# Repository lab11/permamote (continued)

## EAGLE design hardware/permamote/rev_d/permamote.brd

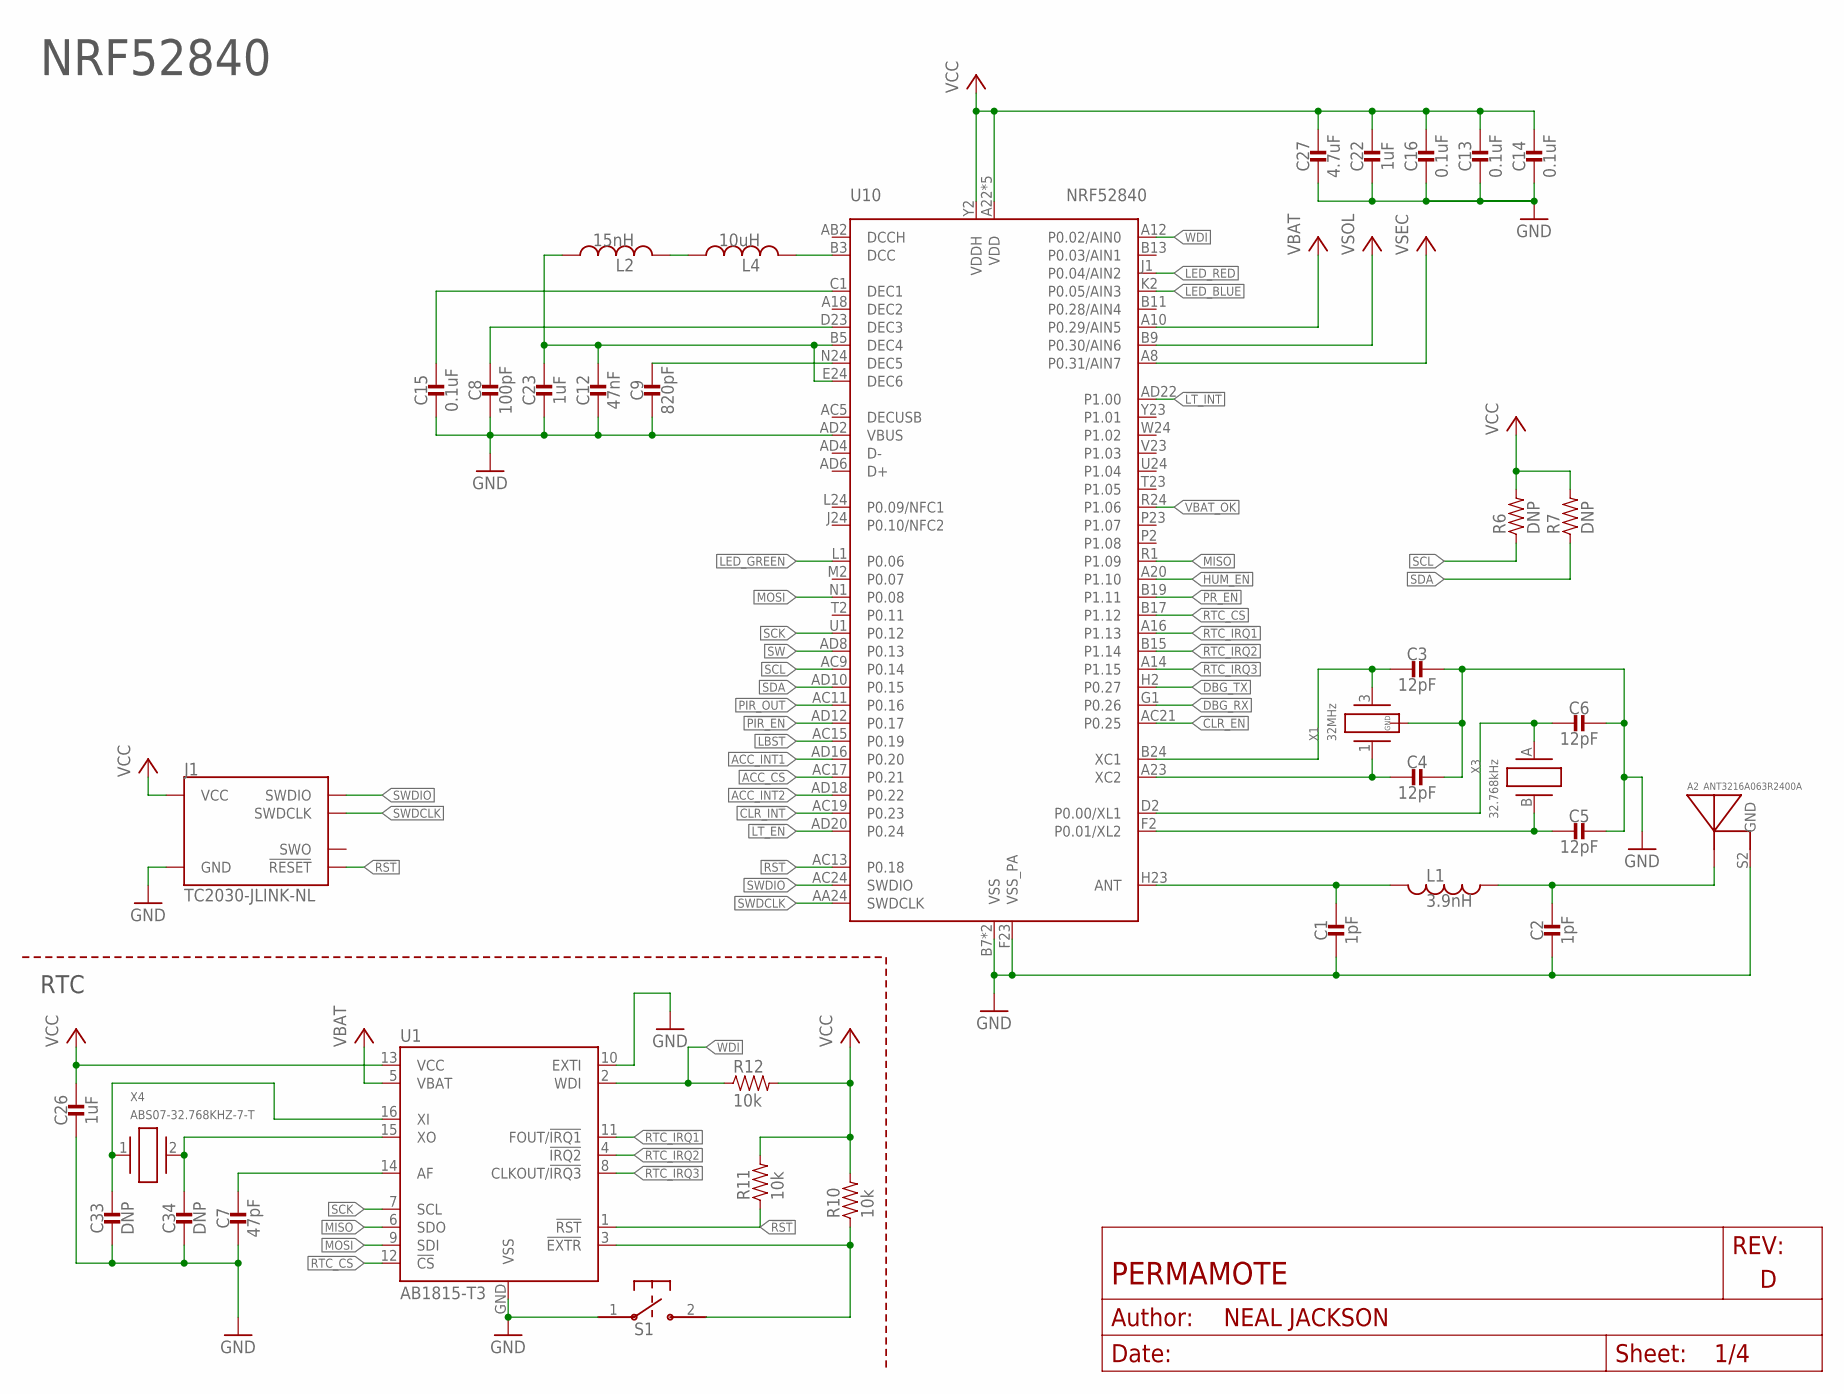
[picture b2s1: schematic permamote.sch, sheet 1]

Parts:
A2: ANT3216A063R2400A
C1, C2: 1pF; 0402_CAP; MPN CL05C010CB5NNNC; DIGIKEY 1276-1595-1-ND
C3, C4, C5, C6: 12pF; 0402_CAP; MPN GRM1555C1H120GA01D; DIGIKEY 490-6197-1-ND
C7: 47pF; 0402_CAP; MPN GRM1555C1H470JA01D; DIGIKEY 490-5942-1-ND
C8: 100pF; 0402_CAP; MPN GRM1555C1H101JA01D; DIGIKEY 490-5922-1-ND
C9: 820pF; 0402_CAP; MPN CL05B821KO5NNNC; DIGIKEY 1276-6535-1-ND
C12: 47nF; 0402_CAP; MPN C1005X7R1C473K050BC; DIGIKEY 445-1264-1-ND
C13, C14, C15, C16: 0.1uF; 0402_CAP; MPN GRM155R71C104KA88J; DIGIKEY 490-6328-1-ND
C22, C23, C26: 1uF; 0402_CAP; MPN GRM155R70G105KA12D; DIGIKEY 490-7195-1-ND
C27: 4.7uF; 0402_CAP; MPN C1005X5R0J475K050BC; DIGIKEY 445-5947-1-ND
C33, C34: DNP; 0402_CAP
J1: TC2030-JLINK-NL; TC2030-IDC-NL
L1: 3.9nH; 0402_CAP; MPN LQP15MN3N9B02D; DIGIKEY 490-1131-1-ND
L2: 15nH; 0402_CAP; MPN HK100515NJ-T; DIGIKEY 587-1521-1-ND
L4: 10uH; 0603_CAP; MPN LQM18FN100M00D; DIGIKEY 490-4025-1-ND
R6, R7: DNP; 0402_RES; MPN RC0402JR-0710KL; DIGIKEY 311-10KJRCT-ND
R10, R11, R12: 10k; 0402_RES; MPN RC0402JR-0710KL; DIGIKEY 311-10KJRCT-ND
S1: B3U-1000P
U1: AB1815-T3; QFN-16-3MM
U10: NRF52840; AQFN73
X1: 32MHz; TXC-7V
X3: 32.768kHz; ABS05
X4: ABS07-32.768KHZ-7-T; 2-SMD

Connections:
!CLR_EN: U10.AC21 (P0.25); also elsewhere on the board
!CLR_INT: U10.AC19 (P0.23); also elsewhere on the board
!HUM_EN: U10.A20 (P1.10); also elsewhere on the board
!LT_EN: U10.AD20 (P0.24); also elsewhere on the board
!LT_INT: U10.AD22 (P1.00); also elsewhere on the board
!PIR_EN: U10.AD12 (P0.17); also elsewhere on the board
!PR_EN: U10.B19 (P1.11); also elsewhere on the board
!RST: J1.3 (!RESET), R11.1, U1.1 (!RST), U10.AC13 (P0.18); also elsewhere on the board
!RTC_EXTR: R10.1, S1.2, U1.3 (!EXTR)
!RTC_IRQ1: U1.11 (FOUT/!IRQ1), U10.A16 (P1.13); also elsewhere on the board
!RTC_IRQ2: U1.4 (!IRQ2), U10.B15 (P1.14); also elsewhere on the board
!RTC_IRQ3: U1.8 (CLKOUT/!IRQ3), U10.A14 (P1.15); also elsewhere on the board
ACC_CS: U10.AC17 (P0.21); also elsewhere on the board
ACC_INT1: U10.AD16 (P0.20); also elsewhere on the board
ACC_INT2: U10.AD18 (P0.22); also elsewhere on the board
DBG_RX: U10.G1 (P0.26)
DBG_TX: U10.H2 (P0.27)
GND: A2.S2 (GND), C1.2, C2.2, C3.1, C4.1, C5.1, C6.1, C7.2, C8.2, C9.2, C12.2, C13.2, C14.2, C15.2, C16.2, C22.2, C23.2, C26.2, C27.2, C33.2, C34.2, J1.5 (GND), S1.1, U1.10 (EXTI), U1.GND (VSS), U10.AD2 (VBUS), U10.B7 (VSS), U10.F23 (VSS_PA), U10.GND (VSS), X1.2 (GND), X1.4 (GND); also elsewhere on the board
LBST: U10.AC15 (P0.19); also elsewhere on the board
LED_BLUE: U10.K2 (P0.05/AIN3); also elsewhere on the board
LED_GREEN: U10.L1 (P0.06); also elsewhere on the board
LED_RED: U10.J1 (P0.04/AIN2); also elsewhere on the board
MISO: U1.6 (SDO), U10.R1 (P1.09); also elsewhere on the board
MOSI: U1.9 (SDI), U10.N1 (P0.08); also elsewhere on the board
unnamed: C9.1, U10.N24 (DEC5)
unnamed: C15.1, U10.C1 (DEC1)
unnamed: C12.1, C23.1, L2.1, U10.B5 (DEC4), U10.E24 (DEC6)
unnamed: C8.1, U10.D23 (DEC3)
unnamed: C1.1, L1.2, U10.H23 (ANT)
unnamed: A2.S1 (ANTENNA), C2.1, L1.1
unnamed: C3.2, U10.B24 (XC1), X1.3 (2)
unnamed: C4.2, U10.A23 (XC2), X1.1
unnamed: C7.1, U1.14 (AF)
unnamed: C33.1, U1.16 (XI), X4.1
unnamed: C34.1, U1.15 (XO), X4.2
unnamed: L4.2, U10.B3 (DCC)
unnamed: L2.2, L4.1
PIR_OUT: U10.AC11 (P0.16); also elsewhere on the board
RTC_CS: U1.12 (!CS), U10.B17 (P1.12); also elsewhere on the board
SCK: U1.7 (SCL), U10.U1 (P0.12); also elsewhere on the board
SCL: R6.1, U10.AC9 (P0.14); also elsewhere on the board
SDA: R7.1, U10.AD10 (P0.15); also elsewhere on the board
SW: U10.AD8 (P0.13); also elsewhere on the board
SWDCLK: J1.4 (SWDCLK), U10.AA24 (SWDCLK)
SWDIO: J1.2 (SWDIO), U10.AC24 (SWDIO)
VBAT: U1.5 (VBAT), U10.A10 (P0.29/AIN5); also elsewhere on the board
VBAT_OK: U10.R24 (P1.06); also elsewhere on the board
VCC: C13.1, C14.1, C16.1, C22.1, C26.1, C27.1, J1.1 (VCC), R6.2, R7.2, R10.2, R11.2, R12.2, U1.13 (VCC), U10.A22 (VDD), U10.AD14 (VDD), U10.AD23 (VDD), U10.B1 (VDD), U10.W1 (VDD), U10.Y2 (VDDH); also elsewhere on the board
VSEC: U10.A8 (P0.31/AIN7); also elsewhere on the board
VSOL: U10.B9 (P0.30/AIN6); also elsewhere on the board
WDI: R12.1, U1.2 (WDI), U10.A12 (P0.02/AIN0); also elsewhere on the board
XL1: C6.2, U10.D2 (P0.00/XL1), X3.A (1)
XL2: C5.2, U10.F2 (P0.01/XL2), X3.B (2)

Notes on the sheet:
NRF52840
RTC

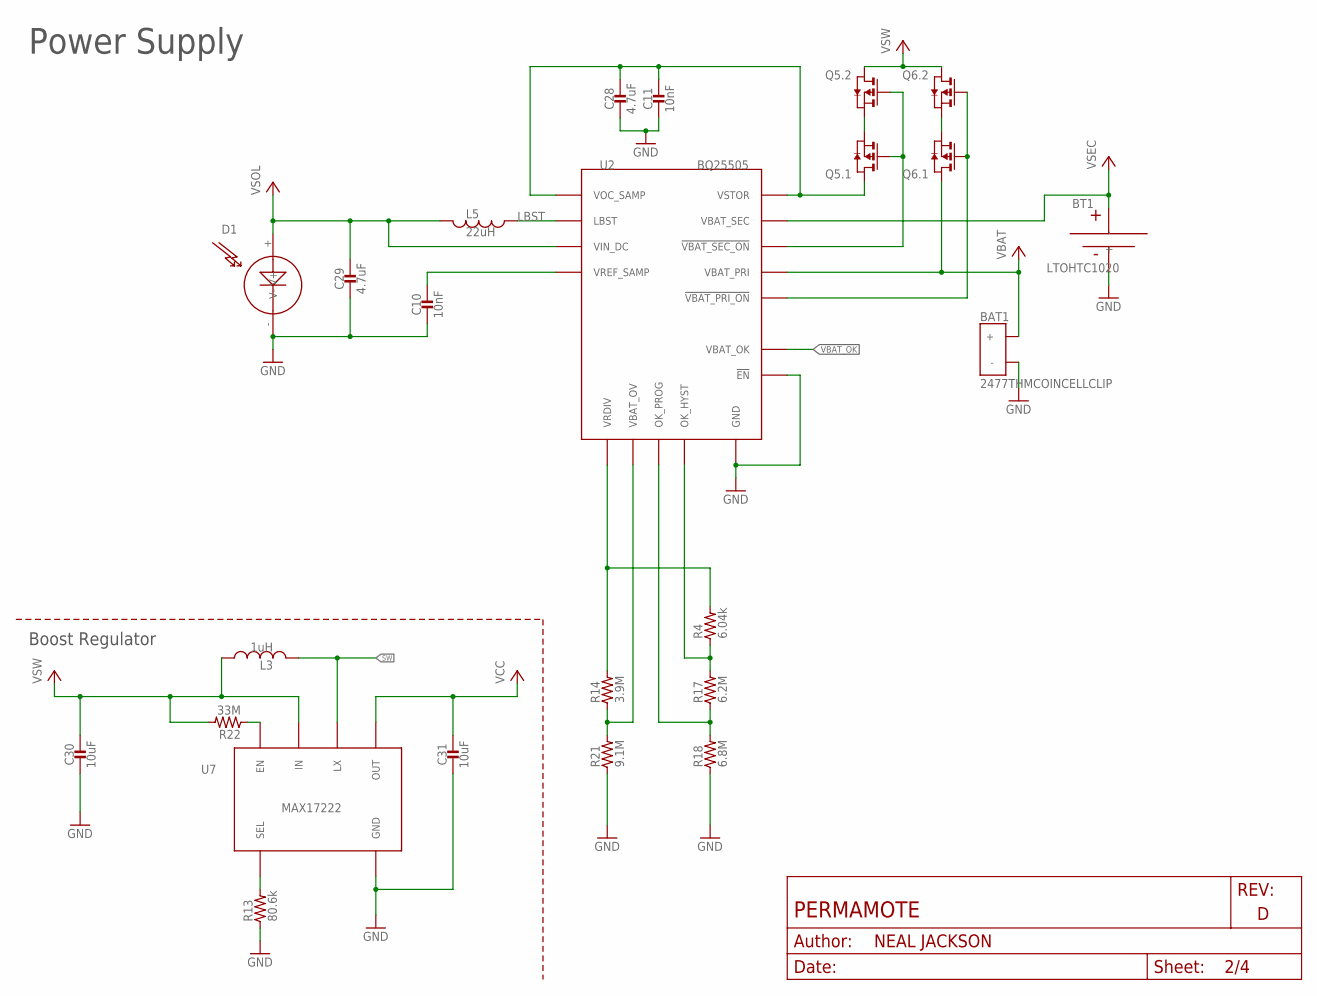
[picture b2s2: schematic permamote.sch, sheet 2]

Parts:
BAT1: 2477THMCOINCELLCLIP; 2477THMCOINCLIP
BT1: LTOHTC1020; 1020
C10, C11: 10nF; 0402_CAP; MPN GRM155R71H103KA88D; DIGIKEY 490-4516-1-ND
C28, C29: 4.7uF; 0402_CAP; MPN C1005X5R0J475K050BC; DIGIKEY 445-5947-1-ND
C30, C31: 10uF; 0603_CAP; MPN GRM188R60J106ME47D; DIGIKEY 490-3896-1-ND
D1: SOLARCELLHOLES; SOLAR_HOLES
L3: 1uH; IHL-1212BZ-11; MPN IHLP1212BZER1R0M11; DIGIKEY 541-1319-1-ND
L5: 22uH; 74437324220; MPN 74437324220; DIGIKEY 732-3340-1-ND
Q5, Q6: PMDXB950UPEL; XDFN-6
R4: 6.04k; 0402_RES; MPN RC0402FR-076K04L; DIGIKEY YAG2293CT-ND
R13: 80.6k; 0603-RES; MPN RC0603FR-0780K6L; DIGIKEY 311-80.6KHRCT-ND
R14: 3.9M; 0402_RES; MPN RC0402JR-073M9L; DIGIKEY YAG3301CT-ND
R17: 6.2M; 0402_RES; MPN RC0402JR-076M2L; DIGIKEY YAG3309CT-ND
R18: 6.8M; 0402_RES; MPN RC0402JR-076M8L; DIGIKEY YAG3310CT-ND
R21: 9.1M; 0402_RES; MPN RC0402JR-079M1L; DIGIKEY YAG3322CT-ND
R22: 33M; 0603-RES; MPN HMC0603JT33M0; DIGIKEY HMC0603JT33M0CT-ND
U2: BQ25505; S-PVQFN-N20-RGR
U7: MAX17222; UDFN-6-MAXIM

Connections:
!VBAT_PRI_ON: Q6.2 (G), Q6.5 (G), U2.10 (!VBAT_PRI_ON)
!VBAT_SEC_ON: Q5.2 (G), Q5.5 (G), U2.9 (!VBAT_SEC_ON)
GND: BAT1.GND (-), BT1.-, C10.2, C11.2, C28.2, C29.2, C30.2, C31.2, D1.- (V-), R13.1, R18.1, R21.1, U2.1 (GND), U2.5 (!EN), U2.6 (GND), U2.15 (GND), U2.16 (GND), U2.17 (GND), U2.PAD (GND), U7.3 (GND); also elsewhere on the board
LBST: L5.P$1 (1), U2.20 (LBST); also elsewhere on the board
unnamed: R13.2, U7.4 (SEL)
unnamed: R22.1, U7.6 (EN)
unnamed: R14.1, R21.2, U2.7 (VBAT_OV)
unnamed: R4.2, R14.2, U2.8 (VRDIV)
unnamed: Q5.1 (S), Q5.4 (S)
unnamed: Q6.1 (S), Q6.4 (S)
unnamed: R17.1, R18.2, U2.12 (OK_PROG)
unnamed: R4.1, R17.2, U2.11 (OK_HYST)
SW: L3.P$2 (2), U7.2 (LX); also elsewhere on the board
VBAT: BAT1.1 (+), BAT1.2 (+), Q6.6 (D), U2.14 (VBAT_PRI); also elsewhere on the board
VBAT_OK: U2.13 (VBAT_OK); also elsewhere on the board
VCC: C31.1, U7.1 (OUT); also elsewhere on the board
VOC_SAMP_VSTOR: C11.1, C28.1, Q5.6 (D), U2.3 (VOC_SAMP), U2.19 (VSTOR)
VREF_SAMP: C10.1, U2.4 (VREF_SAMP)
VSEC: BT1.+, U2.18 (VBAT_SEC); also elsewhere on the board
VSOL: C29.1, D1.+ (V+), L5.P$2 (2), U2.2 (VIN_DC); also elsewhere on the board
VSW: C30.1, L3.P$1 (1), Q5.3 (D), Q6.3 (D), R22.2, U7.5 (IN)

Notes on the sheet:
Power Supply
Boost Regulator

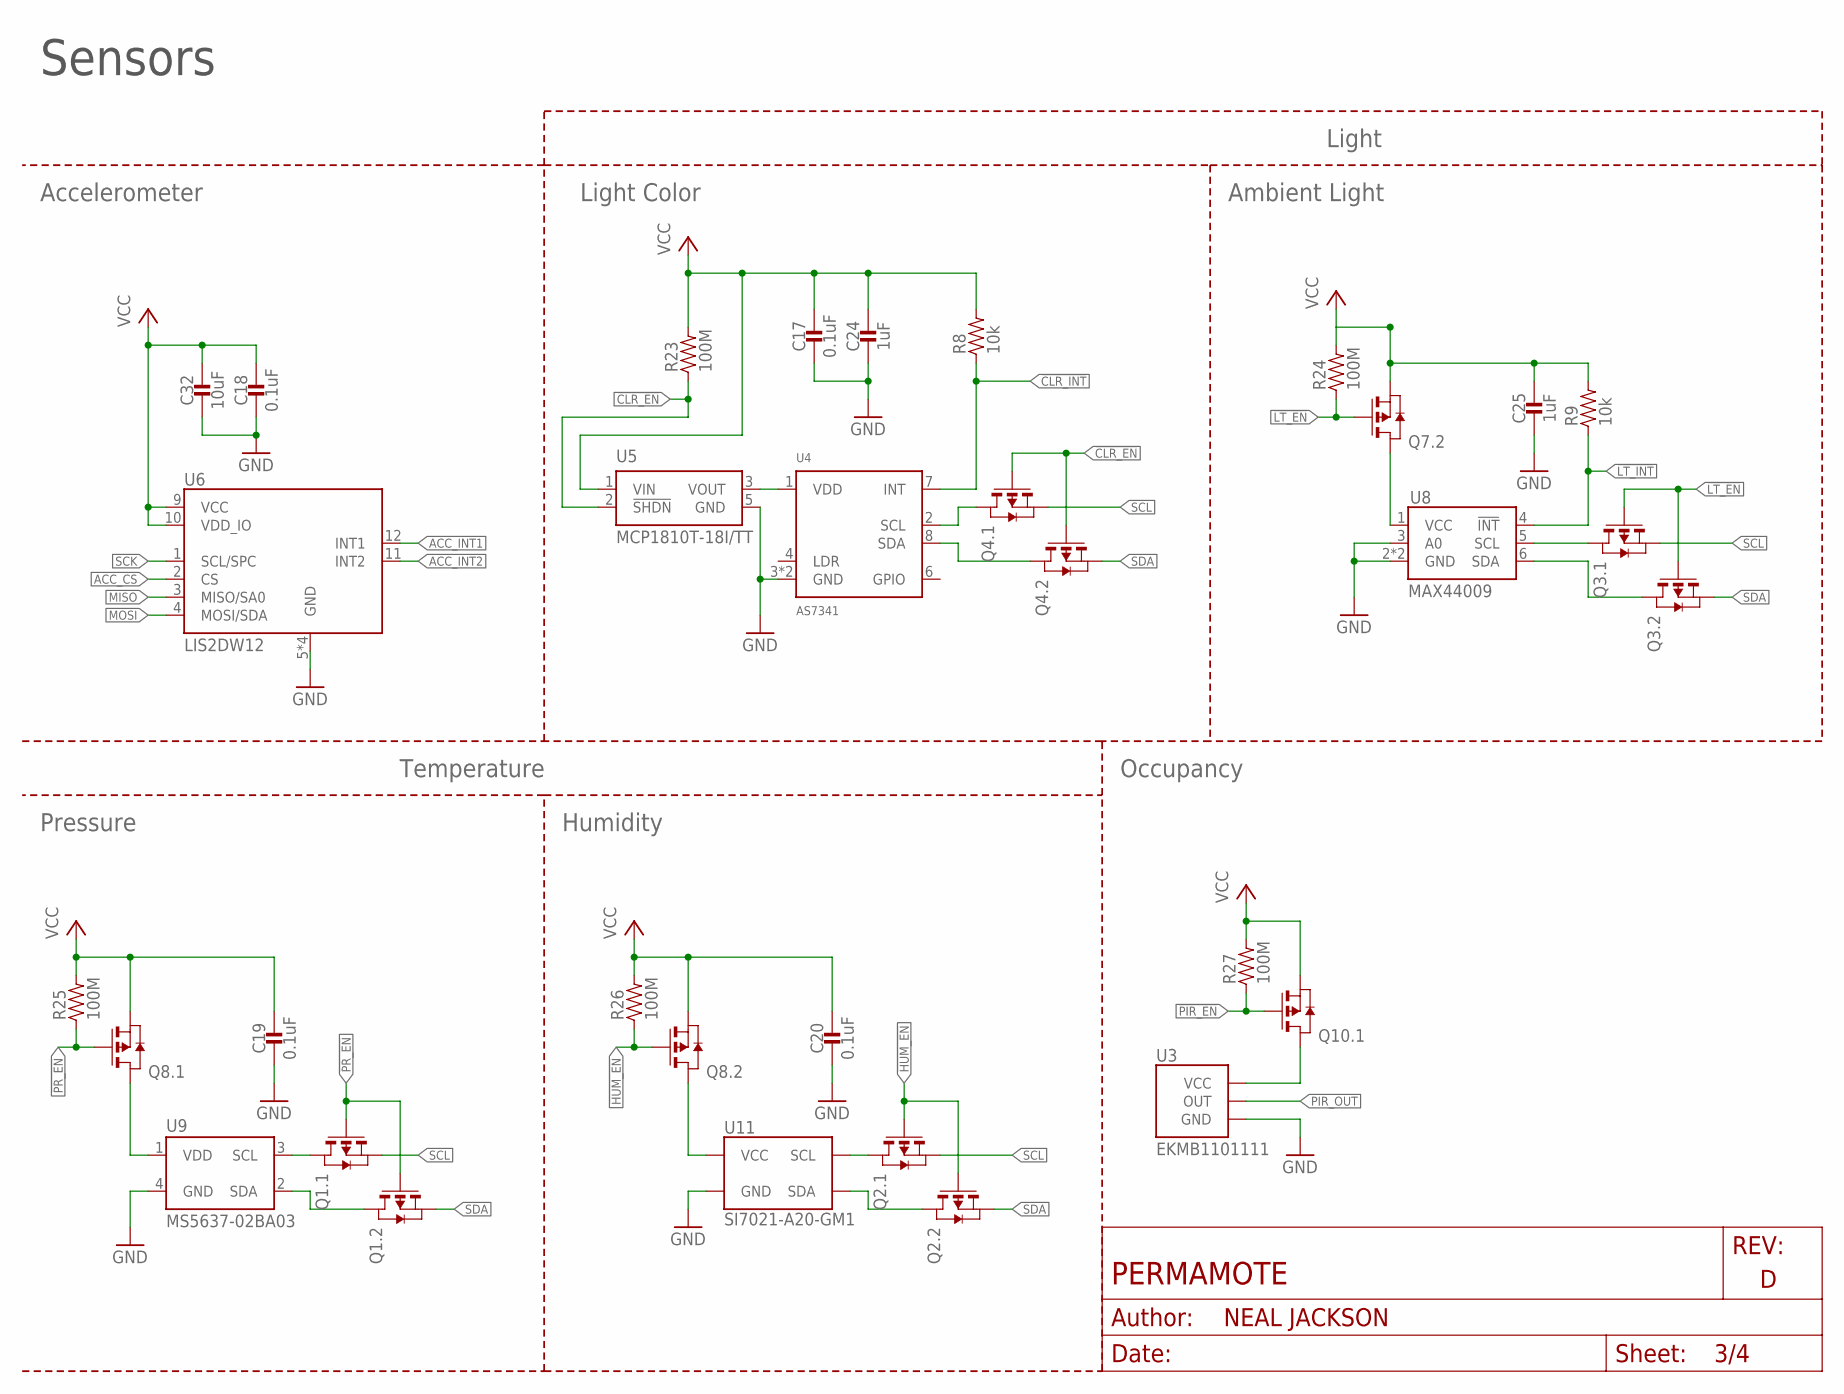
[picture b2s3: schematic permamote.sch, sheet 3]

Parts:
C17, C18, C19, C20: 0.1uF; 0402_CAP; MPN GRM155R71C104KA88J; DIGIKEY 490-6328-1-ND
C24, C25: 1uF; 0402_CAP; MPN GRM155R70G105KA12D; DIGIKEY 490-7195-1-ND
C32: 10uF; 0603_CAP; MPN GRM188R60J106ME47D; DIGIKEY 490-3896-1-ND
Q1, Q2, Q3, Q4, Q7, Q8, Q10: PMDXB950UPEL; XDFN-6
R8, R9: 10k; 0402_RES; MPN RC0402JR-0710KL; DIGIKEY 311-10KJRCT-ND
R23, R24, R25, R26, R27: 100M; 0402_RES; MPN HMC0402JT100M; DIGIKEY 541-100MAHCT-ND
U3: EKMB1101111; AMN2
U4: AS7341; OLGA-8
U5: MCP1810T-18I/TT; SOT-23-5
U6: LIS2DW12; LGA-12
U8: MAX44009; UDFN-6-EXPOSED
U9: MS5637-02BA03; 4-SMD
U11: SI7021-A20-GM1; DFN-6/3MM; MPN SI7021-A20-GM1

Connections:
!CLR_EN: Q4.2 (G), Q4.5 (G), R23.1, U5.2 (!SHDN); also elsewhere on the board
!CLR_INT: R8.1, U4.7 (INT); also elsewhere on the board
!HUM_EN: Q2.2 (G), Q2.5 (G), Q8.5 (G), R26.1; also elsewhere on the board
!LT_EN: Q3.2 (G), Q3.5 (G), Q7.5 (G), R24.1; also elsewhere on the board
!LT_INT: R9.1, U8.4 (!INT); also elsewhere on the board
!PIR_EN: Q10.2 (G), R27.1; also elsewhere on the board
!PR_EN: Q1.2 (G), Q1.5 (G), Q8.2 (G), R25.1; also elsewhere on the board
ACC_CS: U6.2 (CS); also elsewhere on the board
ACC_INT1: U6.12 (INT1); also elsewhere on the board
ACC_INT2: U6.11 (INT2); also elsewhere on the board
GND: C17.2, C18.2, C19.2, C20.2, C24.2, C25.2, C32.2, U3.GND, U4.3 (GND), U4.5 (GND), U5.5 (GND), U6.5 (GND), U6.6 (GND), U6.7 (GND), U6.8 (GND), U8.2 (GND), U8.3 (A0), U8.EP (GND), U9.4 (GND), U11.2 (GND); also elsewhere on the board
MISO: U6.3 (MISO/SA0); also elsewhere on the board
MOSI: U6.4 (MOSI/SDA); also elsewhere on the board
unnamed: Q4.3 (D), U4.8 (SDA)
unnamed: Q7.3 (D), U8.1 (VCC)
unnamed: Q8.6 (D), U9.1 (VDD)
unnamed: Q8.3 (D), U11.5 (VCC)
unnamed: Q10.6 (D), U3.VCC
unnamed: U4.1 (VDD), U5.3 (VOUT)
unnamed: Q1.6 (D), U9.3 (SCL)
unnamed: Q1.3 (D), U9.2 (SDA)
unnamed: Q2.3 (D), U11.1 (SDA)
unnamed: Q2.6 (D), U11.6 (SCL)
unnamed: Q3.3 (D), U8.6 (SDA)
unnamed: Q3.6 (D), U8.5 (SCL)
unnamed: Q4.6 (D), U4.2 (SCL)
PIR_OUT: U3.OUT; also elsewhere on the board
SCK: U6.1 (SCL/SPC); also elsewhere on the board
SCL: Q1.1 (S), Q2.1 (S), Q3.1 (S), Q4.1 (S); also elsewhere on the board
SDA: Q1.4 (S), Q2.4 (S), Q3.4 (S), Q4.4 (S); also elsewhere on the board
VCC: C17.1, C18.1, C19.1, C20.1, C24.1, C25.1, C32.1, Q7.4 (S), Q8.1 (S), Q8.4 (S), Q10.1 (S), R8.2, R9.2, R23.2, R24.2, R25.2, R26.2, R27.2, U5.1 (VIN), U6.9 (VCC), U6.10 (VDD_IO); also elsewhere on the board

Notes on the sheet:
Sensors
Accelerometer
Temperature
Humidity
Pressure
Ambient Light
Light Color
Light
Occupancy

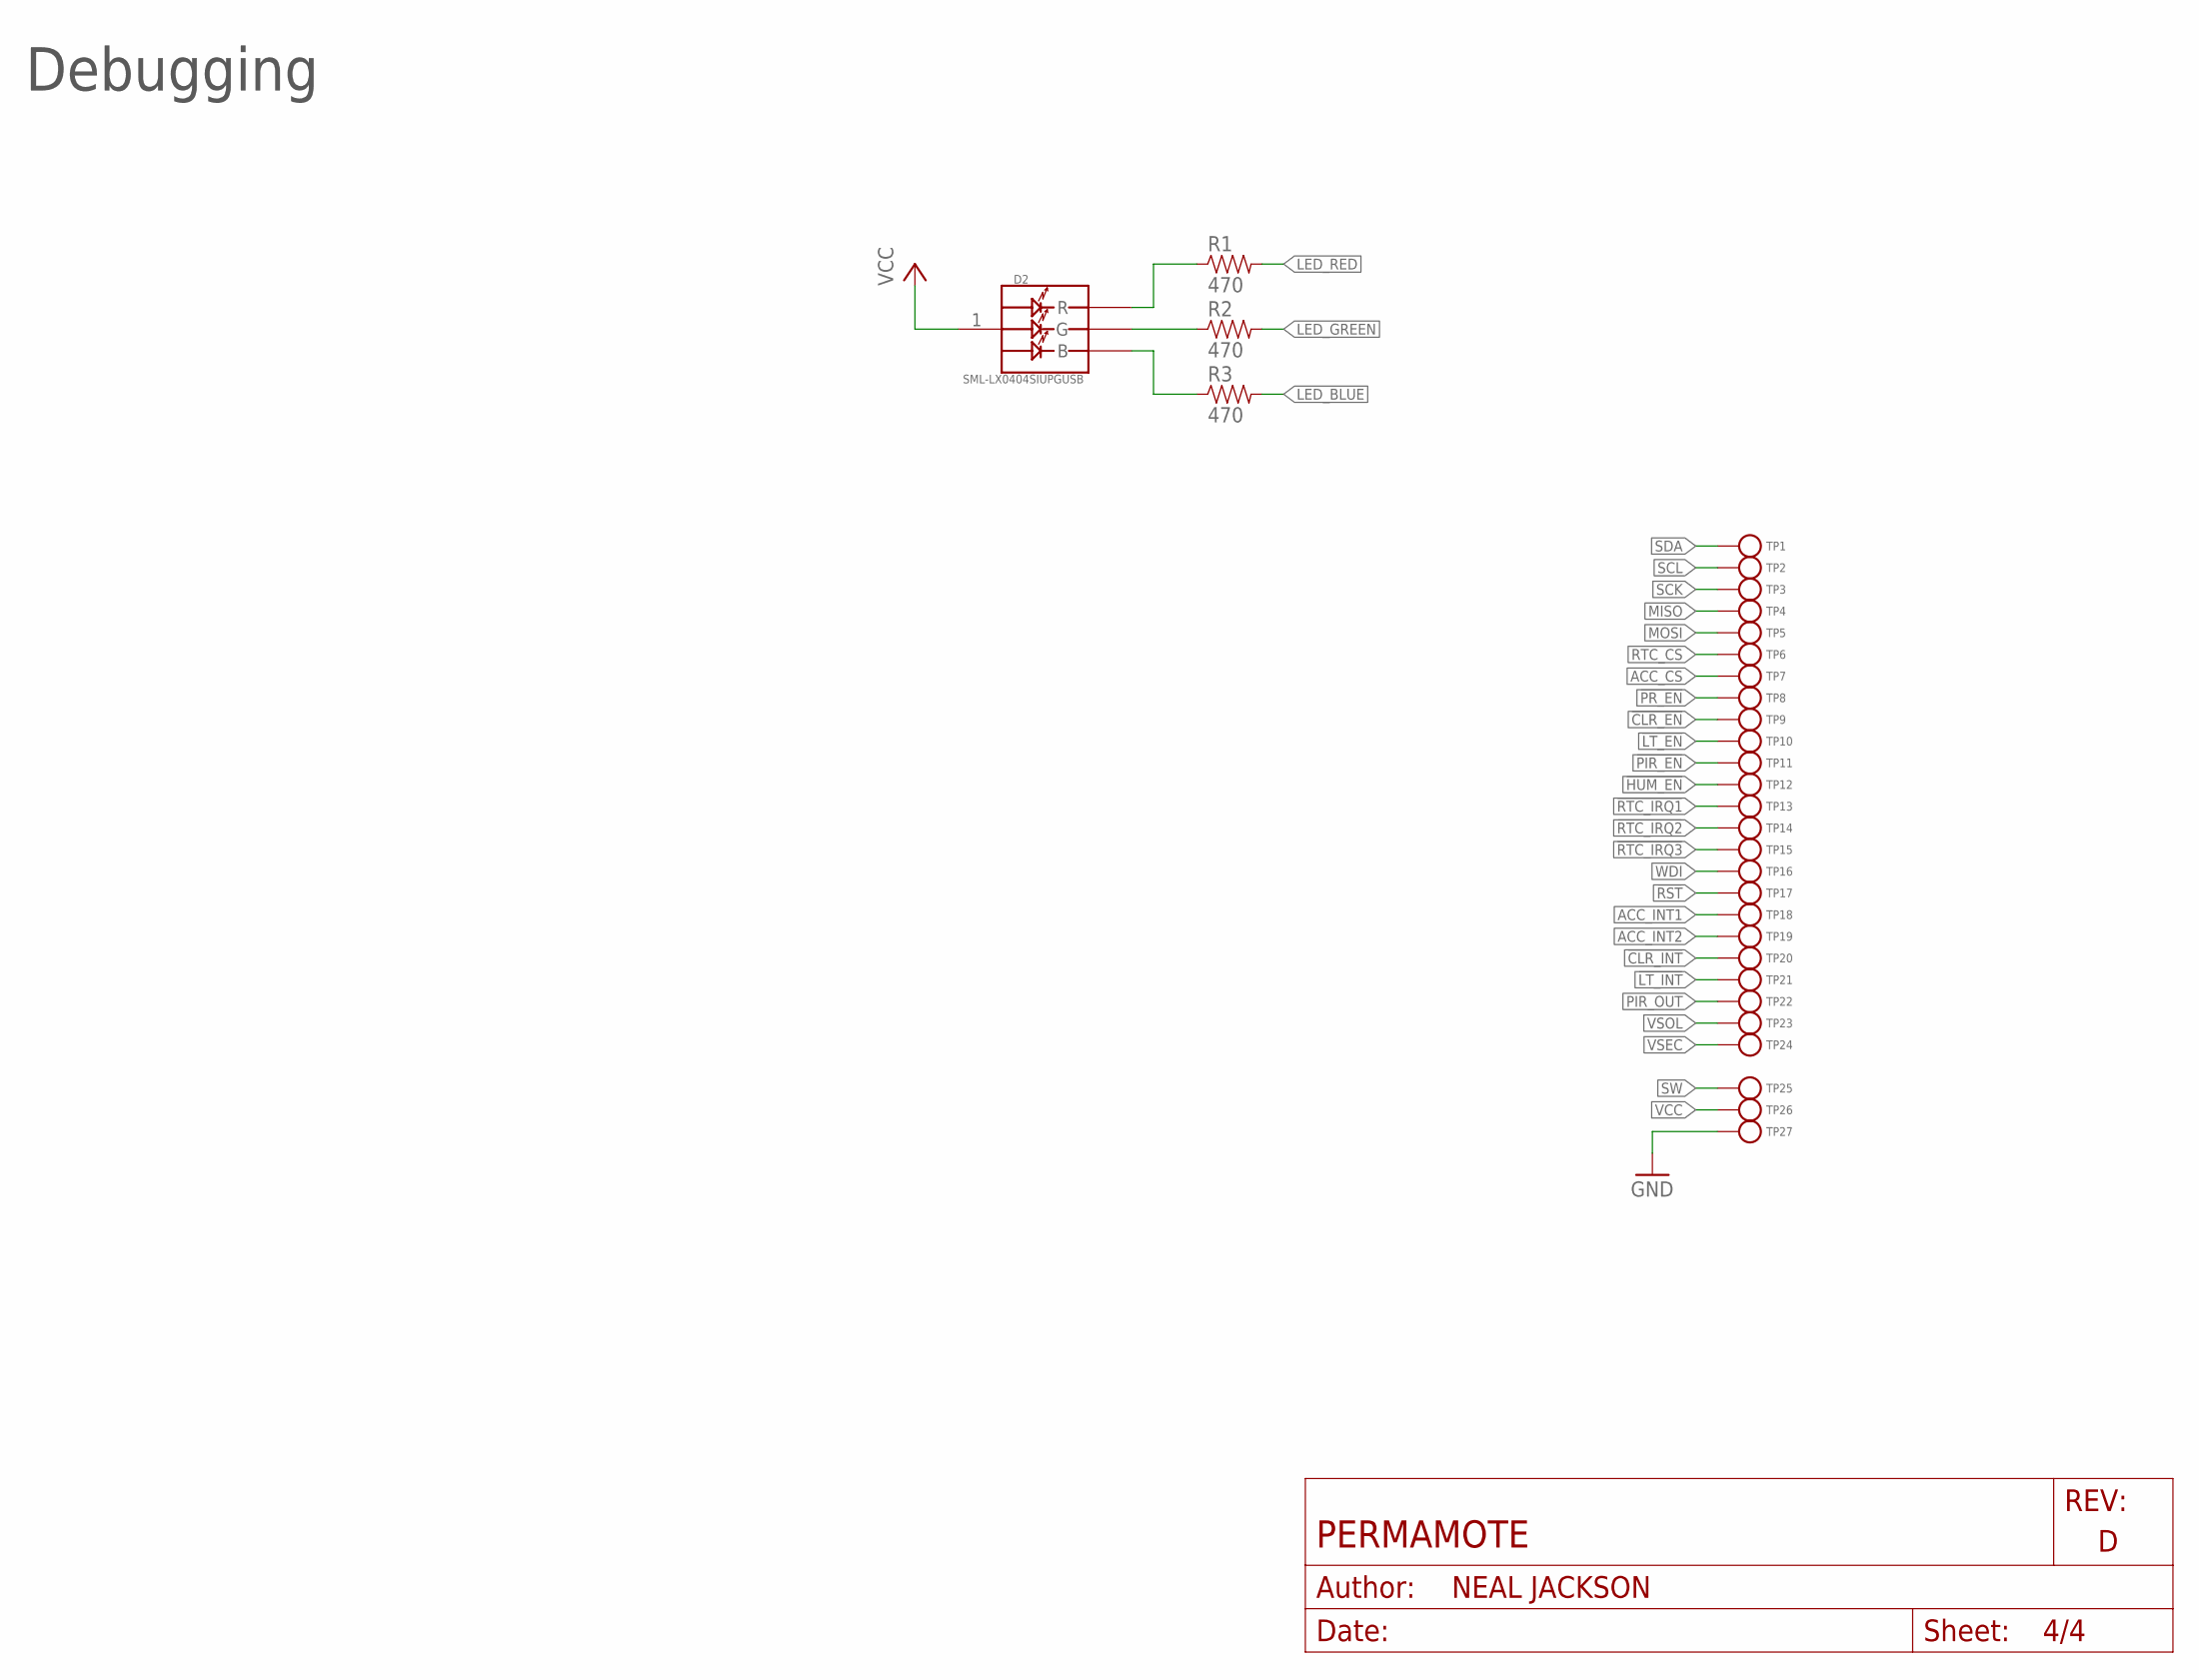
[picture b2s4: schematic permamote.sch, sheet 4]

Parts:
D2: SML-LX0404SIUPGUSB; 1MM_SQ_4PAD
R1, R2, R3: 470; 0402_RES; MPN RC0402JR-07470RL; DIGIKEY 311-470JRCT-ND
TP1, TP2, TP3, TP4, TP5, TP6, TP7, TP8, TP9, TP10, TP11, TP12, TP13, TP14, TP15, TP16, TP17, TP18, TP19, TP20, TP21, TP22, TP23, TP24, TP25, TP26, TP27: TEST-POINT; PAD.03X.03

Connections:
!CLR_EN: TP9.P$1; also elsewhere on the board
!CLR_INT: TP20.P$1; also elsewhere on the board
!HUM_EN: TP12.P$1; also elsewhere on the board
!LT_EN: TP10.P$1; also elsewhere on the board
!LT_INT: TP21.P$1; also elsewhere on the board
!PIR_EN: TP11.P$1; also elsewhere on the board
!PR_EN: TP8.P$1; also elsewhere on the board
!RST: TP17.P$1; also elsewhere on the board
!RTC_IRQ1: TP13.P$1; also elsewhere on the board
!RTC_IRQ2: TP14.P$1; also elsewhere on the board
!RTC_IRQ3: TP15.P$1; also elsewhere on the board
ACC_CS: TP7.P$1; also elsewhere on the board
ACC_INT1: TP18.P$1; also elsewhere on the board
ACC_INT2: TP19.P$1; also elsewhere on the board
GND: TP27.P$1; also elsewhere on the board
LED_BLUE: R3.2; also elsewhere on the board
LED_GREEN: R2.2; also elsewhere on the board
LED_RED: R1.2; also elsewhere on the board
MISO: TP4.P$1; also elsewhere on the board
MOSI: TP5.P$1; also elsewhere on the board
unnamed: D2.2 (R), R1.1
unnamed: D2.4 (G), R2.1
unnamed: D2.3 (B), R3.1
PIR_OUT: TP22.P$1; also elsewhere on the board
RTC_CS: TP6.P$1; also elsewhere on the board
SCK: TP3.P$1; also elsewhere on the board
SCL: TP2.P$1; also elsewhere on the board
SDA: TP1.P$1; also elsewhere on the board
SW: TP25.P$1; also elsewhere on the board
VCC: D2.1 (VDD), TP26.P$1; also elsewhere on the board
VSEC: TP24.P$1; also elsewhere on the board
VSOL: TP23.P$1; also elsewhere on the board
WDI: TP16.P$1; also elsewhere on the board

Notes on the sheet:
Debugging

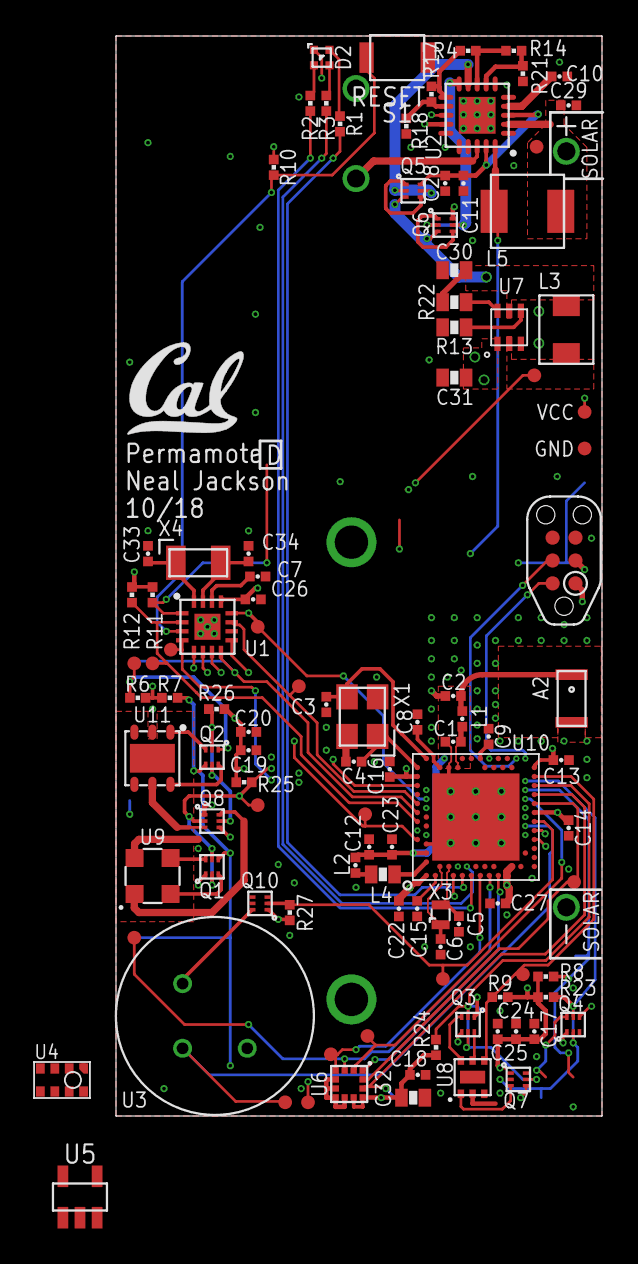
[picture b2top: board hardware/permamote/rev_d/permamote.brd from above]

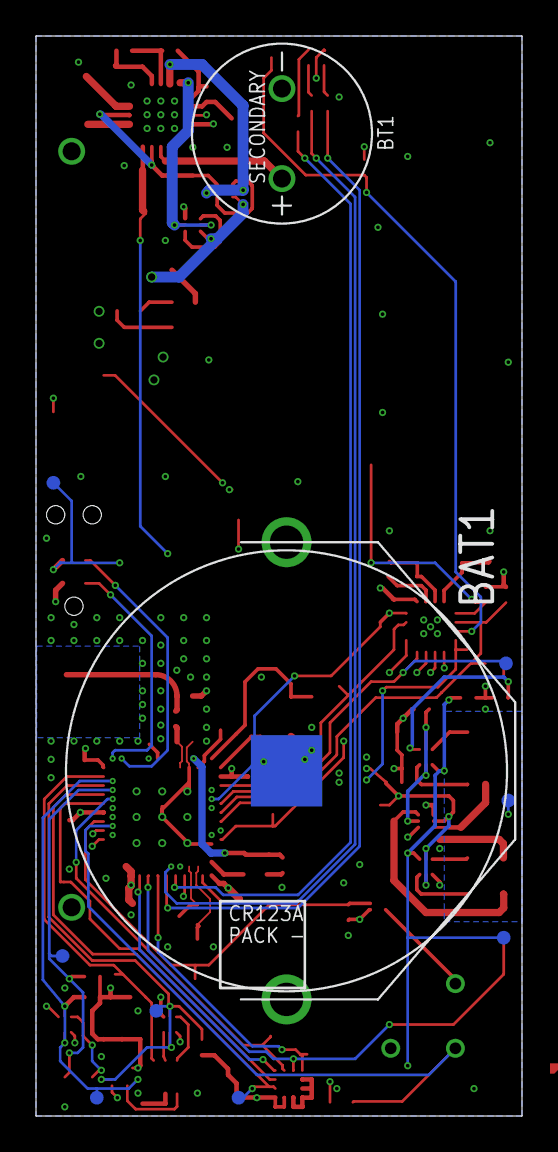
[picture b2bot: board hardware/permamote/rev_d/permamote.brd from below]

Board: 4 copper layers, 27.0 x 60.0 mm, 118 parts (10 on the bottom side), 80 nets.

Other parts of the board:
U$2: UCB_CAL_200MIL

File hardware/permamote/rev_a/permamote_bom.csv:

# Bill of Materials,,,,,,,,,,,,,,
# Converted from {},,,,,,,,,,,,,,
# Generated by bom_to_text.py,,,,,,,,,,,,,,
#,,,,,,,,,,,,,,
,,,,,,,,,,,,,,
Qty,Value,Device,Package,Parts,Description,DIGIKEY,MANUFACTURER,MF,MOUSER,MPN,NEWARK,OC_FARNELL,OC_NEWARK,Notes
9,0.1uF,CAPACITOR0402_CAP,0402_CAP,"C12, C13, C14, C15, C16, C17, C18, C19, C20",SMD Capacitor,490-6328-1-ND,,,,GRM155R71C104KA88J ,,,,
1,0.5pF,CAPACITOR0402_CAP,0402_CAP,C1,SMD Capacitor,490-6264-1-ND,,,,GRM1555C1HR50WA01D ,,,,
1,0.8pF,CAPACITOR0402_CAP,0402_CAP,C2,SMD Capacitor,490-6269-1-ND,,,,GRM1555C1HR80BA01D ,,,,
5,100M,RESISTOR0402_RES,0402_RES,"R23, R24, R25, R26, R27",Resistor,541-100MAHCT-ND,,,,HMC0402JT100M ,,,,
1,100pF,CAPACITOR0402_CAP,0402_CAP,C8,SMD Capacitor,490-5922-1-ND,,,,GRM1555C1H101JA01D ,,,,
7,10k,RESISTOR0402_RES,0402_RES,"R6, R7, R8, R9, R10, R11, R12",Resistor,311-10KJRCT-ND ,,,,RC0402JR-0710KL,,,,Do not populate R6 & R7
2,10nF,CAPACITOR0402_CAP,0402_CAP,"C9, C10",SMD Capacitor,490-4516-1-ND,,,,GRM155R71H103KA88D ,,,,
3,10uF,CAPACITOR0603_CAP,0603_CAP,"C29, C30, C31",SMD Capacitor,490-3896-1-ND,,,,GRM188R60J106ME47D ,,,,
1,10uH,INDUCTOR0603,0603_CAP,L4,A very specific inductor,490-4025-1-ND,,,,LQM18FN100M00D ,,,,
4,12pF,CAPACITOR0402_CAP,0402_CAP,"C3, C4, C5, C6",SMD Capacitor,490-6197-1-ND,,,,GRM1555C1H120GA01D ,,,,
1,15nH,INDUCTOR0402,0402_CAP,L2,A very specific inductor,587-1521-1-ND,,,,HK100515NJ-T ,,,,
5,1uF,CAPACITOR0402_CAP,0402_CAP,"C21, C22, C23, C24, C25",SMD Capacitor,490-7195-1-ND ,,,,GRM155R70G105KA12D ,,,,
1,1uH,INDUCTORIHL,IHL-1212BZ-11,L3,A very specific inductor,541-1319-1-ND,Vishay Dale,,,IHLP1212BZER1R0M11,,,,
1,22uH,INDUCTOR74437324220,74437324220,L5,A very specific inductor,732-3340-1-ND,,,,74437324220,,,,
1,3.3nH,INDUCTOR0402,0402_CAP,L1,A very specific inductor,535-10426-1-ND,,,,AISC-0402-3N3J-T ,,,,
1,3.9M,RESISTOR0402_RES,0402_RES,R14,Resistor,YAG3301CT-ND,,,,RC0402JR-073M9L,,,,
1,32.768kHz,ABS05-32.768KHZ-9-T,ABS05,X3,32.768kHz Crystal,535-11897-1-ND,Abracon,,,ABS05-32.768KHZ-9-T,,,,
1,32MHz,7V-32.000MAHV-T,TXC-7V,X1,TXC CRYSTAL SMD,887-2568-1-ND,TXC CORPORATION,,,7M-32.000MAHV-T,,,,
1,33M,RESISTOR0603_RES,0603-RES,R22,Resistor,HMC0603JT33M0CT-ND,,,,HMC0603JT33M0 ,,,,
3,4.7uF,CAPACITOR0402_CAP,0402_CAP,"C26, C27, C28",SMD Capacitor,445-5947-1-ND,,,,C1005X5R0J475K050BC ,,,,
3,470,RESISTOR0402_RES,0402_RES,"R1, R2, R3",Resistor,311-470JRCT-ND,,,,RC0402JR-07470RL ,,,,
1,47nF,CAPACITOR0402_CAP,0402_CAP,C11,SMD Capacitor,445-1264-1-ND,,,,C1005X7R1C473K050BC ,,,,
1,47pF,CAPACITOR0402_CAP,0402_CAP,C7,SMD Capacitor,490-5942-1-ND,,,,GRM1555C1H470JA01D ,,,,
1,6.04k,RESISTOR0402_RES,0402_RES,R4,Resistor,YAG2293CT-ND,,,,RC0402FR-076K04L,,,,
1,6.2M,RESISTOR0402_RES,0402_RES,R17,Resistor,YAG3309CT-ND,,,,RC0402JR-076M2L,,,,
1,6.8M,RESISTOR0402_RES,0402_RES,R18,Resistor,YAG3310CT-ND,,,,RC0402JR-076M8L,,,,
1,80.6k,RESISTOR0603_RES,0603-RES,R13,Resistor,311-80.6KHRCT-ND,,,,RC0603FR-0780K6L ,,,,
1,9.1M,RESISTOR0402_RES,0402_RES,R21,Resistor,YAG3322CT-ND,,,,RC0402JR-079M1L,,,,
1,AB1815-T3,AB1815-T3,QFN-16-3MM,U1,Ultra-low current RTC. 55nA quiescent @ 3V. 1.5-3.6V input.,535-11936-1-ND,Abracon,,,AB1815-T3,,,,
1,ABS07-32.768KHZ-7-T,ABS07-32.768KHZ-7-T,2-SMD,X4,32.768kHz Crystal,535-9543-1-ND,ABRACON,,,ABS07-32.768KHZ-7-T ,,,,
1,ANT3216A063R2400A,ANT3216A063R2400A,ANT3216A063R2400A,A2,Yageo 2.4GHz,311-1542-1-ND,YAGEO,,,ANT3216A063R2400A,,,,
2,BAT-HLD-002-THM,BAT-HLD-002-THM,BAT-HLD-002-THM,"BT2, BT3",RETAINER BATT CR2016 PC PINS,BAT-HLD-001-THM-ND,,,712-BAT-HLD-001-THM,BAT-HLD-001-THM,,,,Do not populate
1,BAT_PACKCR123A,BAT_PACKCR123A,BH123A,BT4,collection of battery footprints,BH123A-ND,MPD,,,BH123A,,,,Do not populate
1,BQ25505,BQ25505,S-PVQFN-N20-RGR,U2,EH front end for switching between primary and secondary cells,296-37078-1-ND,TI,,,BQ25505RGRR,,,,
2,DNP,CAPACITOR0402_CAP,0402_CAP,"C32, C33",SMD Capacitor,,,,,,,,,Do not populate
5,DNP,RESISTOR0402_RES,0402_RES,"R5, R15, R16, R19, R20",Resistor,YAG3306CT-ND,,,,,,,,Do not populate
1,EKMB1101111,EKMB1101111,AMN2,U3,Passive infrared human detection sensor with built-in amp.,255-3065-ND,PANASONIC,,,EKMB1101111,,,,
1,EVQP2,EVQP2,EVQP2,S1,SWITCH TACTILE SPST-NO 0.02A 15V,P11084SCT-ND,,,,EVQ-P2K02Q ,,,,
1,FT232RQ,FT232RQ,QFN32,U4,Source: http://www.ftdichip.com/Documents/DataSheets/DS_FT232R_v104.pdf,,,,,FT232RQ,,1146033,91K9919,
1,ISL29125,ISL29125,ODFN-6-1.5MMX1.6MM,U5,low power i2c color sensor,ISL29125IROZ-T7ACT-ND ,INTERSIL,,,ISL29125IROZ-T7A,,,,Will Consign (Part is out of stock everywhere)
1,LIS2DW12,LIS2DW12,LGA-12,U6,ultra low power 3 axis accelerometer,,STMicroelectronics,,511-LIS2DW12TR,LIS2DW12TR,,,,
1,LTOHTC1020,LTOHTC1020,1020,BT1,,,,,,,,,,Do not populate
1,MAX17222,MAX17222,UDFN-6-MAXIM,U7,"Very high efficiency, very low power boost converter suitable for EH applications",MAX17222ELT+TCT-ND,MAXIM INTEGRATED,,,MAX17222ELT+T,,,,
1,MAX44009,MAX44009,UDFN-6-EXPOSED,U8,low power ambient light sensor,MAX44009EDT+TCT-ND,MAXIM,,,MAX44009EDT+T,,,,
1,MICRO_USB_B_HIROSE_ZX62R-B-5P(30),MICRO_USB_B_HIROSE_ZX62R-B-5P(30),MICRO_USB_B_HIROSE_ZX62R-B-5P(30),J5,USB Micro B Connector,H125274CT-ND,,,798-ZX62R-B-5P30,ZX62R-B-5P(30),84Y6712,,,
1,MS5637-02BA03,MS5637-02BA03,4-SMD,U9,low power pressure sensor,223-1199-1-ND,TE CONNECTIVITY,,,MS563702BA03-50,,,,
1,NRF52840,NRF52840,AQFN73,U10,"ultra-low power 2.4 GHz wireless system on chip (SoC) integrating a multiprotocol 2.4 GHz transceiver, an ARM® Cortex®-M4F CPU.",1490-1071-1-ND,NORIDIC SEMICONDUCTOR,,,NRF52840,,,,Will Consign (Part is not yet in production)
9,PMDXB950UPEL,PMDXB950UPEL,XDFN-6,"Q1, Q2, Q3, Q4, Q5, Q6, Q7, Q8, Q10","20 V 500mA, dual P-channel Trench MOSFET",1727-2601-1-ND,NEXPERIA,,,PMDXB950UPELZ,,,,
1,SI7021-A20-GM1,SI7021-A20-GM1,DFN-6/3MM,U11,IC TEMP SENSOR RH 2% DFN,336-3141-ND,,,634-SI7021-A20-GM1,SI7021-A20-GM1 ,,,,
1,SML-LX0404SIUPGUSB,SML-LX0404SIUPGUSB,1MM_SQ_4PAD,D2,1mm^2 RGB LED,67-2125-1-ND,Lumex Opto,,,SML-LX0404SIUPGUSB,,,,
1,SOLARCELLHOLES,SOLARCELLHOLES,SOLAR_HOLES,D1,Generic solar cell,,,,,,,,,Do not populate
